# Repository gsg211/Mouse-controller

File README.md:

# Mouse Controller with Arduino and Python 🖱️💻

This project is a simple mouse controller built using an Arduino and Python. The Arduino reads input from sensors or buttons, and the Python script translates those inputs into mouse movements and actions on your computer.

## Project Overview 🌟

- **Arduino Part:** Handles sensor/button inputs and communicates with the computer via serial.
- **Python Part:** Receives serial data from the Arduino and uses it to control the mouse with the `pyautogui` library.

---

## Arduino Setup  🔧

### Breadboard Setup
Refer to the following image for the breadboard wiring:

### PCB Setup
For a more permanent build, you can use the provided PCB design:

- **Schematic:**
  
- **PCB Layout:**

---

## Python Setup 🐍

### Required Libraries
Make sure you have the following Python libraries installed:

```
# Libraries:
├── pyserial
└── pyautogui
```

### Running the Script ▶️
1. Connect your Arduino to your computer.
2. Upload the appropriate sketch to the Arduino.
3. Make sure to select the right serial port in the python script
4. Run the Python script:

```bash
python mouse_controller.py
```

---

## How It Works
- The Arduino reads input from connected components (e.g., joystick, buttons, or sensors).
- It sends the data to the computer over the serial port.
- The Python script reads this data and translates it into mouse actions using `pyautogui`.

---

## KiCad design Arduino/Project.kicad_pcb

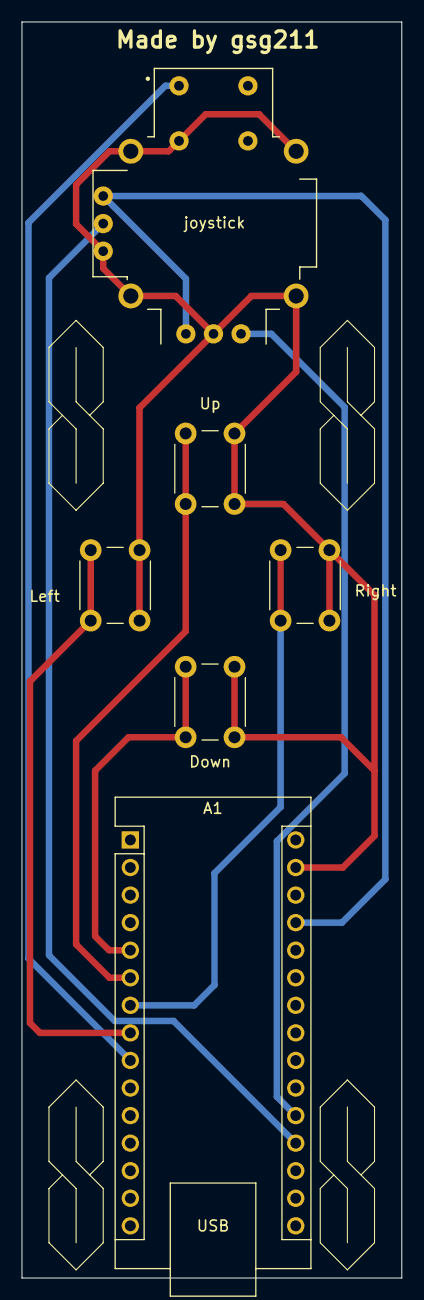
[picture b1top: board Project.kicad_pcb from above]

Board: 2 copper layers, 35.0 x 115.8 mm, 6 parts (0 on the bottom side), 9 nets.

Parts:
A1: Arduino_Nano_v3.x; Arduino_Nano
Down: SW_Push; SW_PUSH_6mm
Left: SW_Push; SW_PUSH_6mm
Right: SW_Push; SW_PUSH_6mm
Up: SW_Push; SW_PUSH_6mm
joystick: COM-09032; XDCR_COM-09032

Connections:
down: A1.5 (D2), Down.1
gnd: A1.29 (GND), Down.2, Left.2, Right.2, Up.2, joystick.B2A (SEL-), joystick.H2 (H), joystick.S1 (SHIELD), joystick.S2 (SHIELD), joystick.S3 (SHIELD), joystick.S4 (SHIELD), joystick.V3 (V-)
hor: A1.20 (A1), joystick.H3 (H-)
left: A1.8 (D5), Left.1
right: A1.7 (D4), Right.1
sel: A1.9 (D6), joystick.B1A (SEL+)
up: A1.6 (D3), Up.1
vcc: A1.27 (+5V), joystick.H1 (H+), joystick.V1 (V+)
vert: A1.19 (A0), joystick.V2 (V)

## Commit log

2024-03-24 Frietzing schematic
2024-07-01 Pcb design + kicad schematic
